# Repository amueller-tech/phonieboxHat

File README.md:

# phonieboxHat
A RaspberryPi Hat for the Phoniebox

Documentation: http://phoniebox.amueller.org

This is a KiCad project for a RaspberryPi Hat to build a Phoniebox, which
basically is a Jukebox for Kids (http://phoniebox.de/)

The PCB can be stacked to a RaspberryPi and offers interfaces connect Buttons,
LEDs, a I2C Display and an OnOffShim. 

Current version is: 0.3, release 2020-06-13

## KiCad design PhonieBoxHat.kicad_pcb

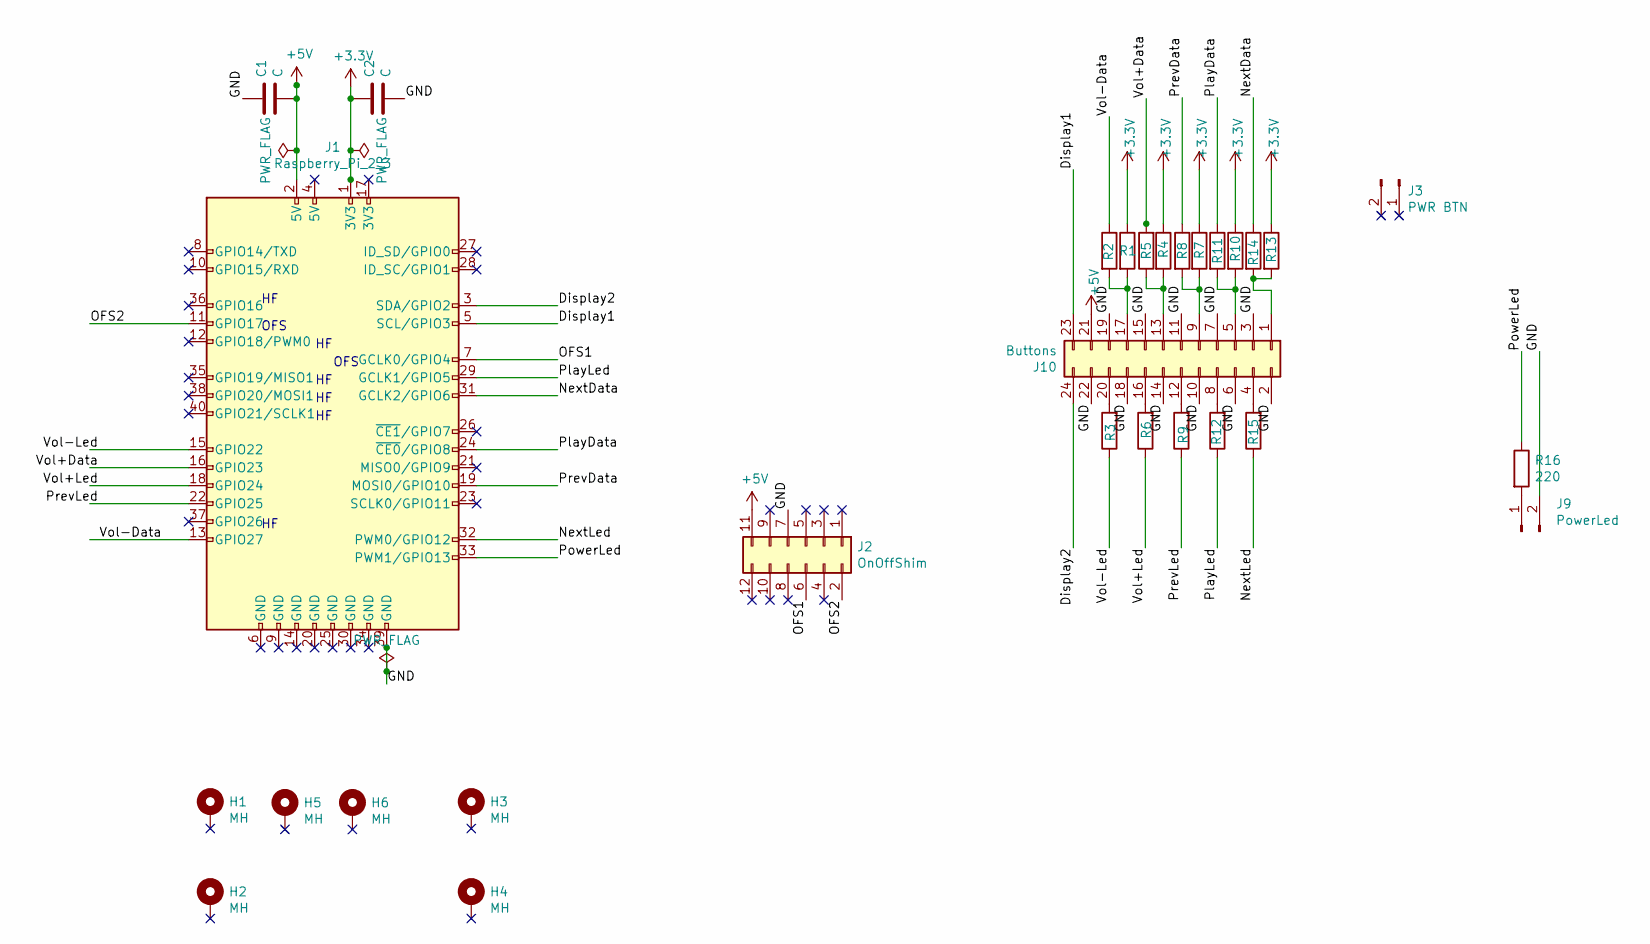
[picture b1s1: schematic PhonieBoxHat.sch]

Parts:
C1, C2: C; C_1206_3216Metric_Pad1.42x1.75mm_HandSolder
H1, H2, H3, H4, H5, H6: MH; MountingHole_3mm_Pad
J1: Raspberry_Pi_2_3; PinSocket_2x20_P2.54mm_Vertical
J2: OnOffShim; PinHeader_2x06_P2.54mm_Vertical
J3: PWR BTN; PinSocket_1x02_P2.54mm_Vertical
J9: PowerLed; PinHeader_1x02_P2.54mm_Horizontal
J10: Buttons; PinHeader_2x12_P2.54mm_Horizontal
R1, R4, R7, R10, R13: 10K; R_1206_3216Metric_Pad1.42x1.75mm_HandSolder
R2, R5, R8, R11, R14: 1K; R_1206_3216Metric_Pad1.42x1.75mm_HandSolder
R3, R6, R9, R12, R15, R16: 220; R_1206_3216Metric_Pad1.42x1.75mm_HandSolder

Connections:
+3V3: C2.1, J1.1 (3V3), R1.1, R4.1, R7.1, R10.1, R13.1
+5V: C1.2, J1.2 (5V), J2.11, J10.21
/Display1: J1.5 (SCL/GPIO3), J10.23
/Display2: J1.3 (SDA/GPIO2), J10.24
/GND: C1.1, C2.2, J1.39 (GND), J2.7, J9.2, J10.2, J10.3, J10.6, J10.7, J10.10, J10.11, J10.14, J10.15, J10.18, J10.19, J10.22
/NextData: J1.31 (GCLK2/GPIO6), R14.1
/NextLed: J1.32 (PWM0/GPIO12), R15.1
/OFS1: J1.7 (GCLK0/GPIO4), J2.6
/OFS2: J1.11 (GPIO17), J2.2
/PlayData: J1.24 (~CE0~/GPIO8), R11.1
/PlayLed: J1.29 (GCLK1/GPIO5), R12.1
/PowerLed: J1.33 (PWM1/GPIO13), R16.1
/PrevData: J1.19 (MOSI0/GPIO10), R8.1
/PrevLed: J1.22 (GPIO25), R9.1
/Vol+Data: J1.16 (GPIO23), R5.2
/Vol+Led: J1.18 (GPIO24), R6.1
/Vol-Data: J1.13 (GPIO27), R2.1
/Vol-Led: J1.15 (GPIO22), R3.1
unnamed: J9.1, R16.2
unnamed: J10.1, R13.2, R14.2
unnamed: J10.4, R15.2
unnamed: J10.5, R10.2, R11.2
unnamed: J10.8, R12.2
unnamed: J10.9, R7.2, R8.2
unnamed: J10.12, R9.2
unnamed: J10.13, R4.2, R5.1
unnamed: J10.16, R6.2
unnamed: J10.17, R1.2, R2.2
unnamed: J10.20, R3.2

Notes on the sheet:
OFS

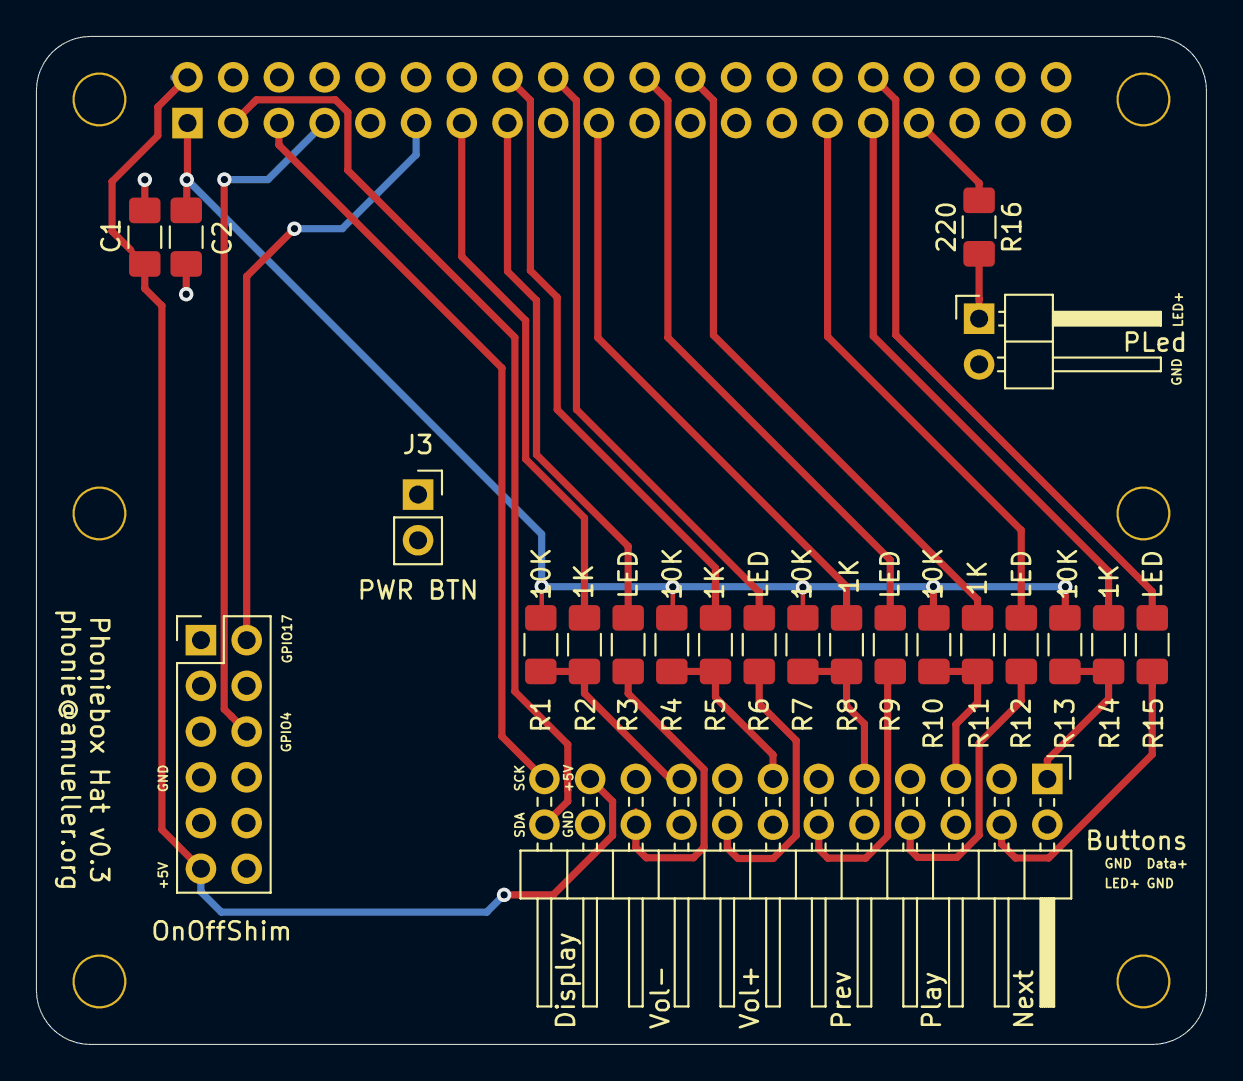
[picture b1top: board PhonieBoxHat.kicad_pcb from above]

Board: 2 copper layers, 65.0 x 56.0 mm, 29 parts (1 on the bottom side), 29 nets.

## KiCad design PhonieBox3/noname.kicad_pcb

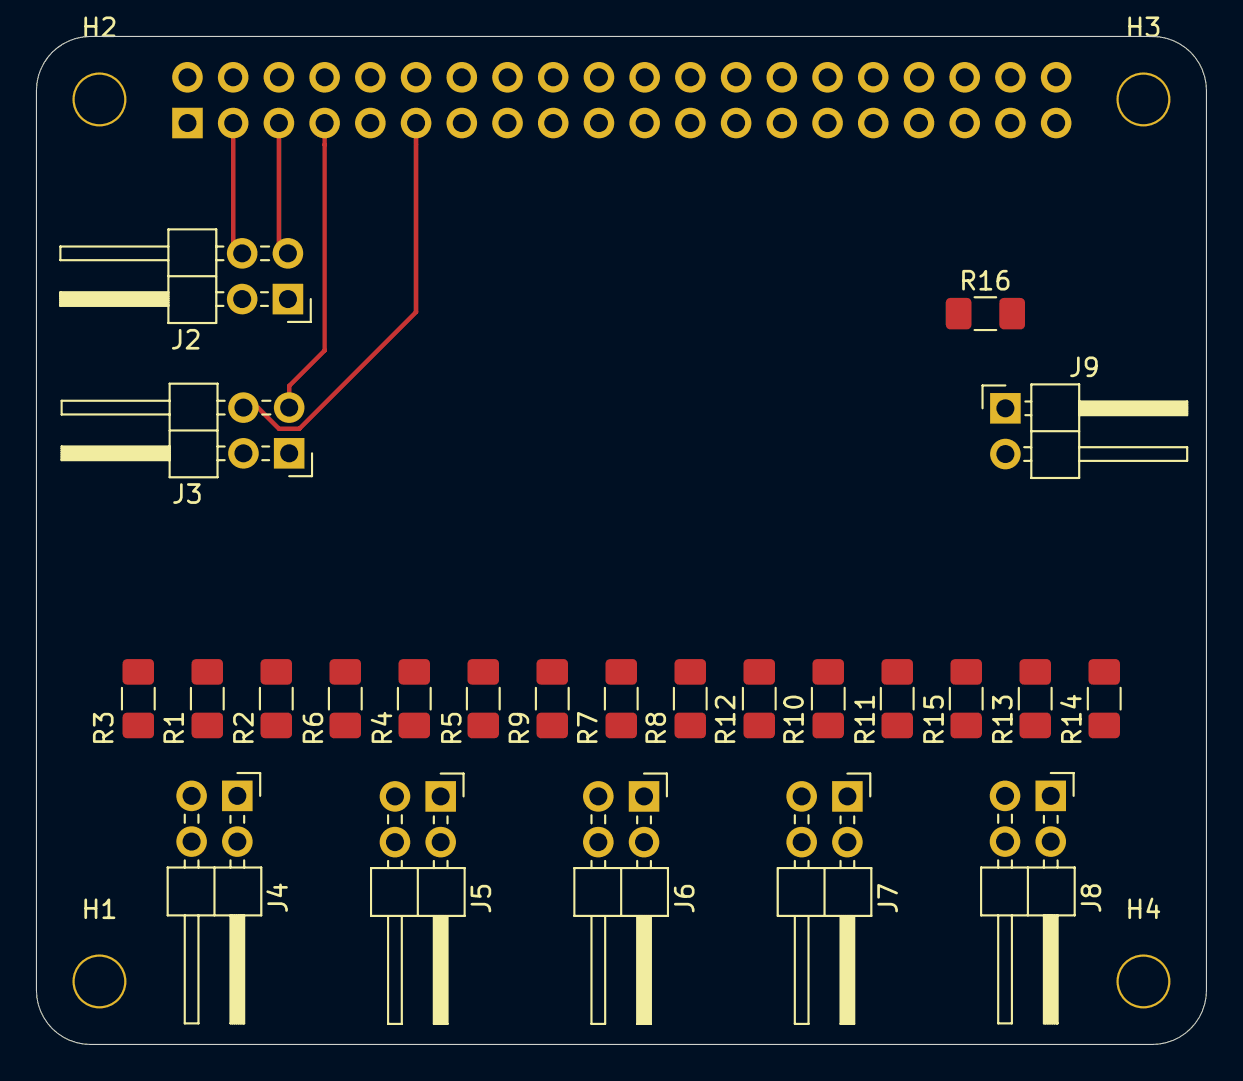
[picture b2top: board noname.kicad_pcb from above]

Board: 2 copper layers, 65.0 x 56.0 mm, 29 parts (1 on the bottom side), 30 nets.

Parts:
H1, H2, H3, H4: MH; MountingHole_3mm_Pad
J1: Raspberry_Pi_2_3; PinSocket_2x20_P2.54mm_Vertical
J2: Display; PinHeader_2x02_P2.54mm_Horizontal
J3: OnOffShim; PinHeader_2x02_P2.54mm_Horizontal
J4: VOL-; PinHeader_2x02_P2.54mm_Horizontal
J5: VOL+; PinHeader_2x02_P2.54mm_Horizontal
J6: Prev; PinHeader_2x02_P2.54mm_Horizontal
J7: Play/Pause; PinHeader_2x02_P2.54mm_Horizontal
J8: Next; PinHeader_2x02_P2.54mm_Horizontal
J9: PowerLed; PinHeader_1x02_P2.54mm_Horizontal
R1, R4, R7, R10, R13: 1K; R_1206_3216Metric_Pad1.42x1.75mm_HandSolder
R2, R5, R8, R11, R14: 10K; R_1206_3216Metric_Pad1.42x1.75mm_HandSolder
R3, R6, R9, R12, R15, R16: 220; R_1206_3216Metric_Pad1.42x1.75mm_HandSolder

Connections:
/3,3V: J1.1, R2.1, R5.1, R8.1, R11.1, R14.1
/5V: J1.2, J2.1, J3.1
/Display1: J1.5, J2.3
/Display2: J1.3, J2.4
/GND: J1.6, J2.2, J3.2, J4.2, J4.3, J5.2, J5.3
/GND2: J1.39, J6.2, J6.3, J7.2, J7.3, J8.2, J8.3, J9.2
/NextData: J1.31, R13.2
/NextLed: J1.32, R15.1
/OFS1: J1.7, J3.3
/OFS2: J1.11, J3.4
/PlayData: J1.24, R10.2
/PlayLed: J1.29, R12.1
/PowerLed: J1.33, R16.1
/PrevData: J1.19, R7.2
/PrevLed: J1.22, R9.1
/Vol+Data: J1.16, R4.2
/Vol+Led: J1.18, R6.1
/Vol-Data: J1.13, R1.2
/Vol-Led: J1.15, R3.1
unnamed: J4.1, R1.1, R2.2
unnamed: J4.4, R3.2
unnamed: J5.1, R4.1, R5.2
unnamed: J5.4, R6.2
unnamed: J6.1, R7.1, R8.2
unnamed: J6.4, R9.2
unnamed: J7.1, R10.1, R11.2
unnamed: J7.4, R12.2
unnamed: J8.1, R13.1, R14.2
unnamed: J8.4, R15.2
unnamed: J9.1, R16.2

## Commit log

2019-11-08 Initial PhonieBoxHat Version
    This is the initial commit of the PhonieBoxHat Version 0.2 that
    I successfully used to build up my Phoniebox as documented here: https://phoniebox.amueller.org
2020-06-13 v0.3
    New version of the PCB to integrate the OnOffShim
2022-04-15 directory cleanup of old version
